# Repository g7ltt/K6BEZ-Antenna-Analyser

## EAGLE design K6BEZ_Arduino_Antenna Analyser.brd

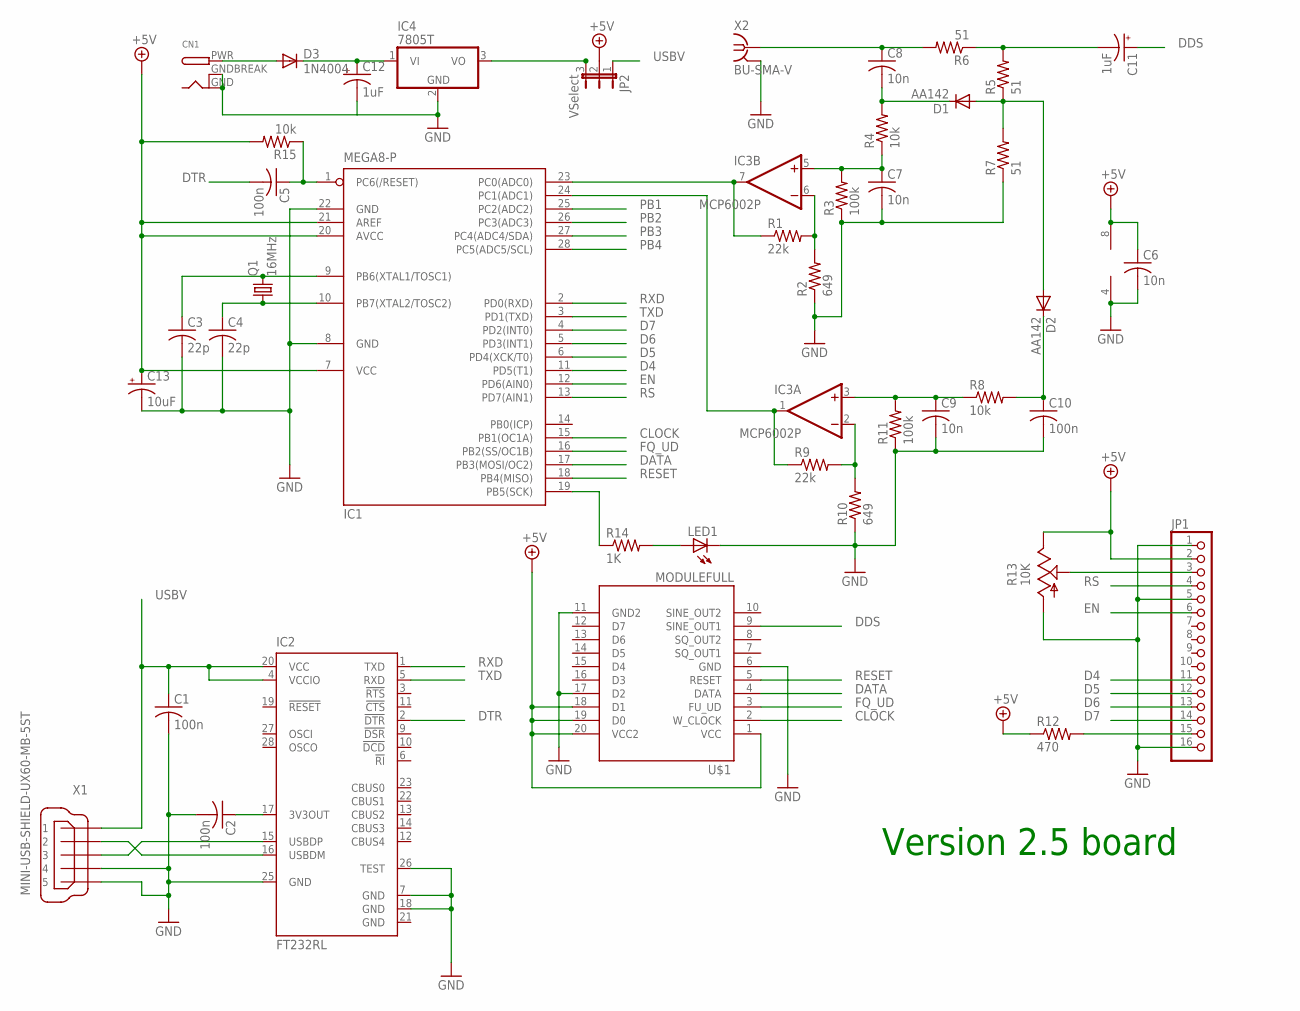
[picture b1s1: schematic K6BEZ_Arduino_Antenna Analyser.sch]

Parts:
C1, C2, C5, C10: 100n; C025-025X050
C3, C4: 22p; C025-025X050
C6, C7, C8, C9: 10n; C025-025X050
C11, C12: 1uF; E2,5-5
C13: 10uF; E2,5-5
CN1: DCBARRELPTH; DCJACK_2MM_PTH
D1, D2: AA142; DO07
D3: 1N4004; DO41-10
IC1: MEGA8-P; DIL28-3
IC2: FT232RL; SSOP28
IC3: MCP6002P; DIL08
IC4: 7805T; TO220H
JP1: PINHD-1X16; 1X16
JP2: VSelect; JP2
LED1: LED3MM
Q1: 16MHz; HC49/S
R1, R9: 22k; 0204/7
R2, R10: 649; 0204/7
R3, R11: 100k; 0204/7
R4, R8, R15: 10k; 0204/7
R5, R6, R7: 51; 0204/7
R12: 470; 0204/7
R13: 10K; CA6V
R14: 1K; 0204/7
U$1: MODULEFULL; MODULE
X1: MINI-USB-SHIELD-UX60-MB-5ST; UX60-MB-5ST
X2: BU-SMA-V

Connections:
+5V: C6.1, C13.+, IC1.7 (VCC), IC1.20 (AVCC), IC1.21 (AREF), IC3.8 (V+), JP1.2, JP2.2, R12.1, R13.E, R15.2, U$1.1 (VCC), U$1.18 (D1), U$1.19 (D0), U$1.20 (VCC2)
CLOCK: IC1.15 (PB1(OC1A)), U$1.2 (W_CLOCK)
D4: IC1.11 (PD5(T1)), JP1.11
D5: IC1.6 (PD4(XCK/T0)), JP1.12
D6: IC1.5 (PD3(INT1)), JP1.13
D7: IC1.4 (PD2(INT0)), JP1.14
DATA: IC1.17 (PB3(MOSI/OC2)), U$1.4 (DATA)
DDS: C11.+, U$1.9 (SINE_OUT1)
DTR: C5.2, IC2.2 (!DTR)
EN: IC1.12 (PD6(AIN0)), JP1.6
FQ_UD: IC1.16 (PB2(SS/OC1B)), U$1.3 (FU_UD)
GND: C1.2, C2.2, C3.2, C4.2, C6.2, C7.2, C9.2, C10.2, C12.-, C13.-, CN1.GND, CN1.GNDBREAK, IC1.8 (GND), IC1.22 (GND), IC2.7 (GND), IC2.18 (GND), IC2.21 (GND), IC2.25 (GND), IC2.26 (TEST), IC3.4 (V-), IC4.2 (GND), JP1.1, JP1.5, JP1.16, LED1.K (C), R2.1, R3.1, R7.1, R10.1, R11.1, R13.A, U$1.6 (GND), U$1.11 (GND2), U$1.17 (D2), X1.4, X1.5, X2.2, X2.3 (2), X2.4 (2), X2.5 (2)
unnamed: C3.1, IC1.9 (PB6(XTAL1/TOSC1)), Q1.2
unnamed: IC2.16 (USBDM), X1.2
unnamed: IC2.15 (USBDP), X1.3
unnamed: C4.1, IC1.10 (PB7(XTAL2/TOSC2)), Q1.1
unnamed: C2.1, IC2.17 (3V3OUT)
unnamed: JP1.15, R12.2
unnamed: IC1.23 (PC0(ADC0)), IC3.7 (OUT), R1.1
unnamed: C5.1, IC1.1 (PC6(/RESET)), R15.1
unnamed: IC3.6 (-IN), R1.2, R2.2
unnamed: C7.1, IC3.5 (+IN), R3.2, R4.1
unnamed: JP1.3, R13.S
unnamed: C8.2, D1.C, R4.2
unnamed: C8.1, R6.2, X2.1
unnamed: C11.-, R5.2, R6.1
unnamed: D1.A, D2.A, R5.1, R7.2
unnamed: LED1.A, R14.2
unnamed: C9.1, IC3.3 (+IN), R8.1, R11.2
unnamed: IC1.24 (PC1(ADC1)), IC3.1 (OUT), R9.1
unnamed: IC1.19 (PB5(SCK)), R14.1
unnamed: C10.1, D2.C, R8.2
unnamed: C12.+, D3.C, IC4.1 (VI)
unnamed: CN1.PWR, D3.A
unnamed: IC4.3 (VO), JP2.3
unnamed: IC3.2 (-IN), R9.2, R10.2
PB1: IC1.25 (PC2(ADC2))
PB2: IC1.26 (PC3(ADC3))
PB3: IC1.27 (PC4(ADC4/SDA))
PB4: IC1.28 (PC5(ADC5/SCL))
RESET: IC1.18 (PB4(MISO)), U$1.5 (RESET)
RS: IC1.13 (PD7(AIN1)), JP1.4
RXD: IC1.2 (PD0(RXD)), IC2.1 (TXD)
TXD: IC1.3 (PD1(TXD)), IC2.5 (RXD)
USBV: C1.1, IC2.4 (VCCIO), IC2.20 (VCC), JP2.1, X1.1

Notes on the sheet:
Version 2.5 board

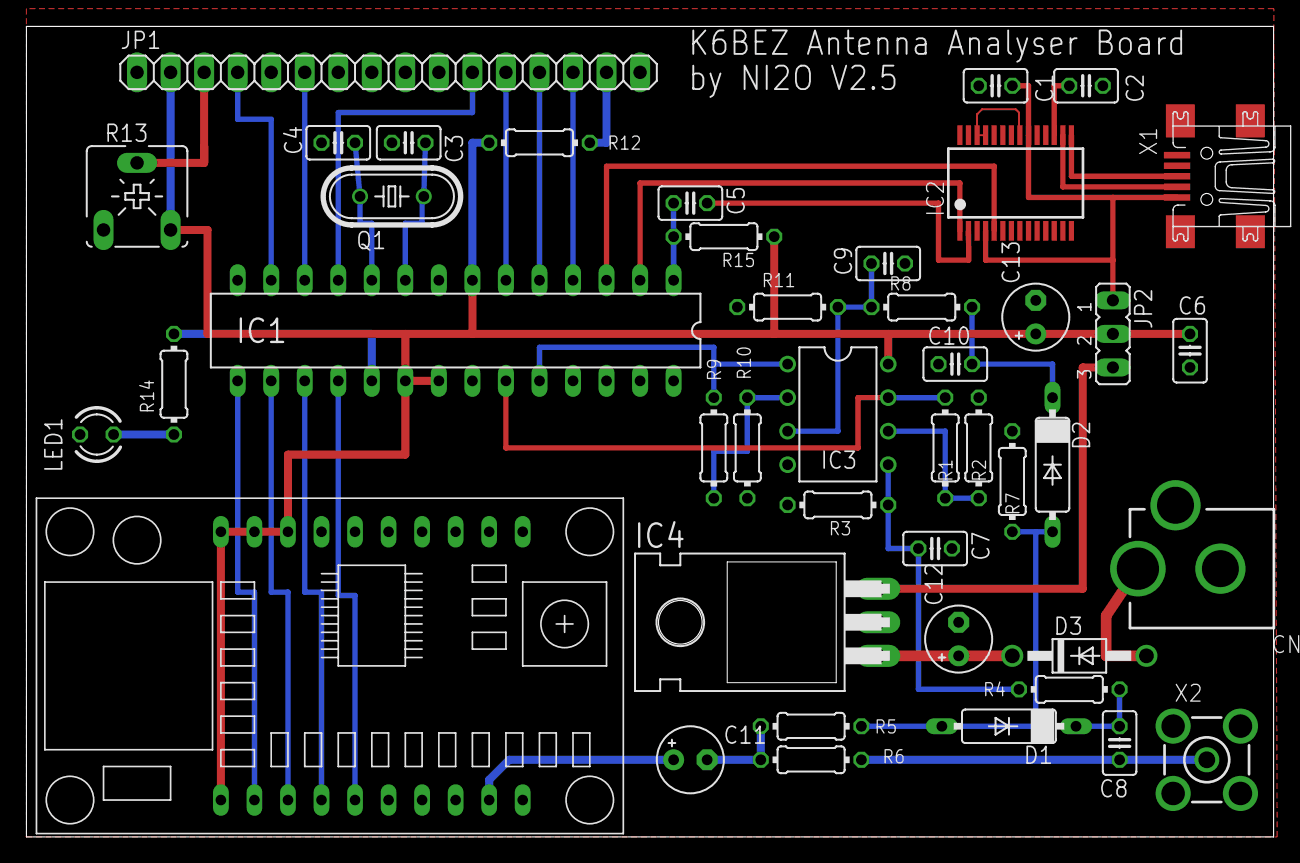
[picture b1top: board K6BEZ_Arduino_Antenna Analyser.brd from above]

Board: 2 copper layers, 94.5 x 61.4 mm, 43 parts (0 on the bottom side), 41 nets.

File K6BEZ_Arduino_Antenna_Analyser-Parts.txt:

Partlist

Exported from K6BEZ_Arduino_Antenna Analyser.sch at 1/20/15 4:04 PM

EAGLE Version 6.6.0 Copyright (c) 1988-2014 CadSoft

Assembly variant: 

Part     Value                       Device                      Package        Library    Sheet

C1       100n                        C-US025-025X050             C025-025X050   resistor   1
C2       100n                        C-US025-025X050             C025-025X050   resistor   1
C3       22p                         C-US025-025X050             C025-025X050   resistor   1
C4       22p                         C-US025-025X050             C025-025X050   resistor   1
C5       100n                        C-US025-025X050             C025-025X050   resistor   1
C6       10n                         C-US025-025X050             C025-025X050   resistor   1
C7       10n                         C-US025-025X050             C025-025X050   resistor   1
C8       10n                         C-US025-025X050             C025-025X050   resistor   1
C9       10n                         C-US025-025X050             C025-025X050   resistor   1
C10      100n                        C-US025-025X050             C025-025X050   resistor   1
C11      1uF                         CPOL-USE2.5-5               E2,5-5         resistor   1
C12      1uF                         CPOL-USE2.5-5               E2,5-5         resistor   1
C14      10uF                        CPOL-USE2.5-5               E2,5-5         resistor   1
CN1                                  DCBARRELPTH                 DCJACK_2MM_PTH adafruit   1
D1       AA142                       AA112                       DO07           diode      1
D2       AA142                       AA112                       DO07           diode      1
D3       1N4004                      1N4004                      DO41-10        diode      1
IC1      MEGA8-P                     MEGA8-P                     DIL28-3        atmel      1
IC2      FT232RL                     FT232RL                     SSOP28         ftdichip   1
IC3      MCP6002P                    MCP602P                     DIL08          linear     1
IC4      7805T                       7805T                       TO220H         linear     1
JP1                                  PINHD-1X16                  1X16           pinhead    1
JP2                                  JP2E                        JP2            jumper     1
LED1                                 LED3MM                      LED3MM         led        1
Q1       16MHz                       CRYSTALHC49S                HC49/S         crystal    1
R1       22k                         R-US_0204/7                 0204/7         rcl        1
R2       649                         R-US_0204/7                 0204/7         rcl        1
R3       100k                        R-US_0204/7                 0204/7         rcl        1
R4       10k                         R-US_0204/7                 0204/7         rcl        1
R5       51                          R-US_0204/7                 0204/7         rcl        1
R6       51                          R-US_0204/7                 0204/7         rcl        1
R7       51                          R-US_0204/7                 0204/7         rcl        1
R8       10k                         R-US_0204/7                 0204/7         rcl        1
R9       22k                         R-US_0204/7                 0204/7         rcl        1
R10      649                         R-US_0204/7                 0204/7         rcl        1
R11      100k                        R-US_0204/7                 0204/7         rcl        1
R12      470                         R-US_0204/7                 0204/7         rcl        1
R13      10K                         TRIM_US-CA6V                CA6V           pot        1
R14      1K                          R-US_0204/7                 0204/7         rcl        1
U$1      MODULEFULL                  MODULEFULL                  MODULE         DDS Module 1
X1       MINI-USB-SHIELD-UX60-MB-5ST MINI-USB-SHIELD-UX60-MB-5ST UX60-MB-5ST    con-hirose 1
X2       BU-SMA-V                    BU-SMA-V                    BU-SMA-V       con-coax   1
